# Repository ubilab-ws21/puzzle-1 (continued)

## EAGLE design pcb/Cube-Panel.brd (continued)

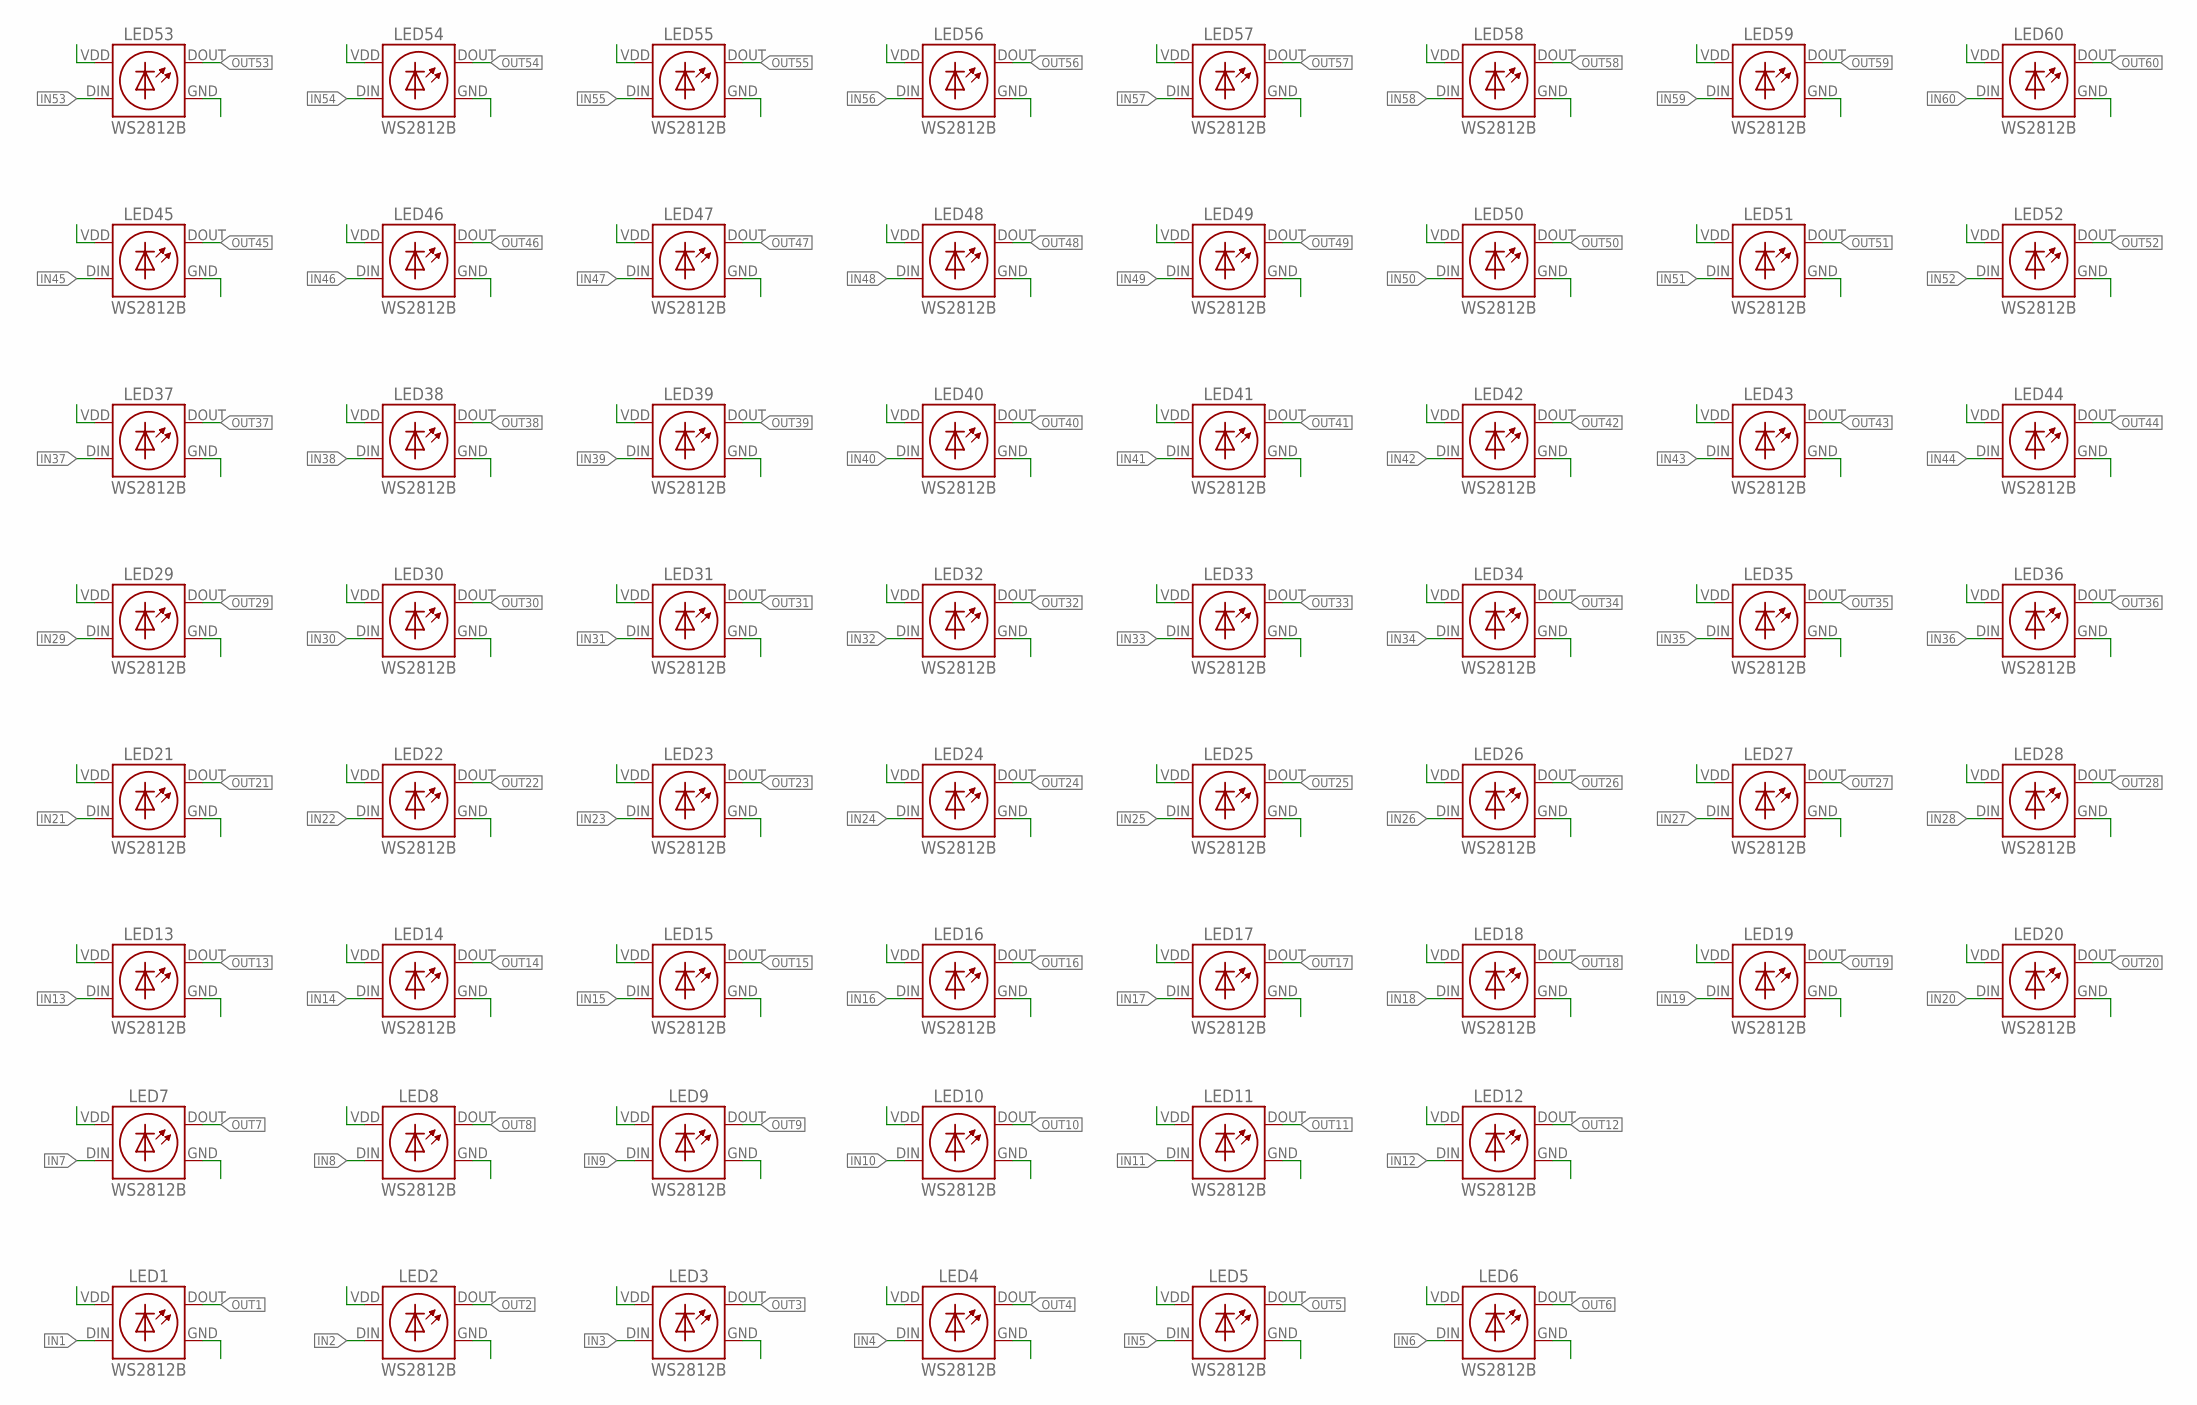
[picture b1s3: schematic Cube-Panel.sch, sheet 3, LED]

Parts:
LED1, LED2, LED3, LED4, LED5, LED6, LED7, LED8, LED9, LED10, LED11, LED12, LED13, LED14, LED15, LED16, LED17, LED18, LED19, LED20, LED21, LED22, LED23, LED24, LED25, LED26, LED27, LED28, LED29, LED30, LED31, LED32, LED33, LED34, LED35, LED36, LED37, LED38, LED39, LED40, LED41, LED42, LED43, LED44, LED45, LED46, LED47, LED48, LED49, LED50, LED51, LED52, LED53, LED54, LED55, LED56, LED57, LED58, LED59, LED60: WS2812B

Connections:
GND: LED1.GND, LED2.GND, LED3.GND, LED4.GND, LED5.GND, LED6.GND, LED7.GND, LED8.GND, LED9.GND, LED10.GND, LED11.GND, LED12.GND, LED13.GND, LED14.GND, LED15.GND, LED16.GND, LED17.GND, LED18.GND, LED19.GND, LED20.GND, LED21.GND, LED22.GND, LED23.GND, LED24.GND, LED25.GND, LED26.GND, LED27.GND, LED28.GND, LED29.GND, LED30.GND, LED31.GND, LED32.GND, LED33.GND, LED34.GND, LED35.GND, LED36.GND, LED37.GND, LED38.GND, LED39.GND, LED40.GND, LED41.GND, LED42.GND, LED43.GND, LED44.GND, LED45.GND, LED46.GND, LED47.GND, LED48.GND, LED49.GND, LED50.GND, LED51.GND, LED52.GND, LED53.GND, LED54.GND, LED55.GND, LED56.GND, LED57.GND, LED58.GND, LED59.GND, LED60.GND; also elsewhere on the board
IN1: LED1.DIN; also elsewhere on the board
IN2: LED2.DIN; also elsewhere on the board
IN3: LED3.DIN; also elsewhere on the board
IN4: LED4.DIN; also elsewhere on the board
IN5: LED5.DIN; also elsewhere on the board
IN6: LED6.DIN; also elsewhere on the board
IN7: LED7.DIN; also elsewhere on the board
IN8: LED8.DIN; also elsewhere on the board
IN9: LED9.DIN; also elsewhere on the board
IN10: LED10.DIN; also elsewhere on the board
IN11: LED11.DIN; also elsewhere on the board
IN12: LED12.DIN; also elsewhere on the board
IN13: LED13.DIN; also elsewhere on the board
IN14: LED14.DIN; also elsewhere on the board
IN15: LED15.DIN; also elsewhere on the board
IN16: LED16.DIN; also elsewhere on the board
IN17: LED17.DIN; also elsewhere on the board
IN18: LED18.DIN; also elsewhere on the board
IN19: LED19.DIN; also elsewhere on the board
IN20: LED20.DIN; also elsewhere on the board
IN21: LED21.DIN; also elsewhere on the board
IN22: LED22.DIN; also elsewhere on the board
IN23: LED23.DIN; also elsewhere on the board
IN24: LED24.DIN; also elsewhere on the board
IN25: LED25.DIN; also elsewhere on the board
IN26: LED26.DIN; also elsewhere on the board
IN27: LED27.DIN; also elsewhere on the board
IN28: LED28.DIN; also elsewhere on the board
IN29: LED29.DIN; also elsewhere on the board
IN30: LED30.DIN; also elsewhere on the board
IN31: LED31.DIN; also elsewhere on the board
IN32: LED32.DIN; also elsewhere on the board
IN33: LED33.DIN; also elsewhere on the board
IN34: LED34.DIN; also elsewhere on the board
IN35: LED35.DIN; also elsewhere on the board
IN36: LED36.DIN; also elsewhere on the board
IN37: LED37.DIN; also elsewhere on the board
IN38: LED38.DIN; also elsewhere on the board
IN39: LED39.DIN; also elsewhere on the board
IN40: LED40.DIN; also elsewhere on the board
IN41: LED41.DIN; also elsewhere on the board
IN42: LED42.DIN; also elsewhere on the board
IN43: LED43.DIN; also elsewhere on the board
IN44: LED44.DIN; also elsewhere on the board
IN45: LED45.DIN; also elsewhere on the board
IN46: LED46.DIN; also elsewhere on the board
IN47: LED47.DIN; also elsewhere on the board
IN48: LED48.DIN; also elsewhere on the board
IN49: LED49.DIN; also elsewhere on the board
IN50: LED50.DIN; also elsewhere on the board
IN51: LED51.DIN; also elsewhere on the board
IN52: LED52.DIN; also elsewhere on the board
IN53: LED53.DIN; also elsewhere on the board
IN54: LED54.DIN; also elsewhere on the board
IN55: LED55.DIN; also elsewhere on the board
IN56: LED56.DIN; also elsewhere on the board
IN57: LED57.DIN; also elsewhere on the board
IN58: LED58.DIN; also elsewhere on the board
IN59: LED59.DIN; also elsewhere on the board
IN60: LED60.DIN; also elsewhere on the board
OUT1: LED1.DOUT; also elsewhere on the board
OUT2: LED2.DOUT; also elsewhere on the board
OUT3: LED3.DOUT; also elsewhere on the board
OUT4: LED4.DOUT; also elsewhere on the board
OUT5: LED5.DOUT; also elsewhere on the board
OUT6: LED6.DOUT; also elsewhere on the board
OUT7: LED7.DOUT; also elsewhere on the board
OUT8: LED8.DOUT; also elsewhere on the board
OUT9: LED9.DOUT; also elsewhere on the board
OUT10: LED10.DOUT; also elsewhere on the board
OUT11: LED11.DOUT; also elsewhere on the board
OUT12: LED12.DOUT; also elsewhere on the board
OUT13: LED13.DOUT; also elsewhere on the board
OUT14: LED14.DOUT; also elsewhere on the board
OUT15: LED15.DOUT; also elsewhere on the board
OUT16: LED16.DOUT; also elsewhere on the board
OUT17: LED17.DOUT; also elsewhere on the board
OUT18: LED18.DOUT; also elsewhere on the board
OUT19: LED19.DOUT; also elsewhere on the board
OUT20: LED20.DOUT; also elsewhere on the board
OUT21: LED21.DOUT; also elsewhere on the board
OUT22: LED22.DOUT; also elsewhere on the board
OUT23: LED23.DOUT; also elsewhere on the board
OUT24: LED24.DOUT; also elsewhere on the board
OUT25: LED25.DOUT; also elsewhere on the board
OUT26: LED26.DOUT; also elsewhere on the board
OUT27: LED27.DOUT; also elsewhere on the board
OUT28: LED28.DOUT; also elsewhere on the board
OUT29: LED29.DOUT; also elsewhere on the board
OUT30: LED30.DOUT; also elsewhere on the board
OUT31: LED31.DOUT; also elsewhere on the board
OUT32: LED32.DOUT; also elsewhere on the board
OUT33: LED33.DOUT; also elsewhere on the board
OUT34: LED34.DOUT; also elsewhere on the board
OUT35: LED35.DOUT; also elsewhere on the board
OUT36: LED36.DOUT; also elsewhere on the board
OUT37: LED37.DOUT; also elsewhere on the board
OUT38: LED38.DOUT; also elsewhere on the board
OUT39: LED39.DOUT; also elsewhere on the board
OUT40: LED40.DOUT; also elsewhere on the board
OUT41: LED41.DOUT; also elsewhere on the board
OUT42: LED42.DOUT; also elsewhere on the board
OUT43: LED43.DOUT; also elsewhere on the board
OUT44: LED44.DOUT; also elsewhere on the board
OUT45: LED45.DOUT; also elsewhere on the board
OUT46: LED46.DOUT; also elsewhere on the board
OUT47: LED47.DOUT; also elsewhere on the board
OUT48: LED48.DOUT; also elsewhere on the board
OUT49: LED49.DOUT; also elsewhere on the board
OUT50: LED50.DOUT; also elsewhere on the board
OUT51: LED51.DOUT; also elsewhere on the board
OUT52: LED52.DOUT; also elsewhere on the board
OUT53: LED53.DOUT; also elsewhere on the board
OUT54: LED54.DOUT; also elsewhere on the board
OUT55: LED55.DOUT; also elsewhere on the board
OUT56: LED56.DOUT; also elsewhere on the board
OUT57: LED57.DOUT; also elsewhere on the board
OUT58: LED58.DOUT; also elsewhere on the board
OUT59: LED59.DOUT; also elsewhere on the board
OUT60: LED60.DOUT; also elsewhere on the board
VCC: LED1.VDD (VCC), LED2.VDD (VCC), LED3.VDD (VCC), LED4.VDD (VCC), LED5.VDD (VCC), LED6.VDD (VCC), LED7.VDD (VCC), LED8.VDD (VCC), LED9.VDD (VCC), LED10.VDD (VCC), LED11.VDD (VCC), LED12.VDD (VCC), LED13.VDD (VCC), LED14.VDD (VCC), LED15.VDD (VCC), LED16.VDD (VCC), LED17.VDD (VCC), LED18.VDD (VCC), LED19.VDD (VCC), LED20.VDD (VCC), LED21.VDD (VCC), LED22.VDD (VCC), LED23.VDD (VCC), LED24.VDD (VCC), LED25.VDD (VCC), LED26.VDD (VCC), LED27.VDD (VCC), LED28.VDD (VCC), LED29.VDD (VCC), LED30.VDD (VCC), LED31.VDD (VCC), LED32.VDD (VCC), LED33.VDD (VCC), LED34.VDD (VCC), LED35.VDD (VCC), LED36.VDD (VCC), LED37.VDD (VCC), LED38.VDD (VCC), LED39.VDD (VCC), LED40.VDD (VCC), LED41.VDD (VCC), LED42.VDD (VCC), LED43.VDD (VCC), LED44.VDD (VCC), LED45.VDD (VCC), LED46.VDD (VCC), LED47.VDD (VCC), LED48.VDD (VCC), LED49.VDD (VCC), LED50.VDD (VCC), LED51.VDD (VCC), LED52.VDD (VCC), LED53.VDD (VCC), LED54.VDD (VCC), LED55.VDD (VCC), LED56.VDD (VCC), LED57.VDD (VCC), LED58.VDD (VCC), LED59.VDD (VCC), LED60.VDD (VCC); also elsewhere on the board

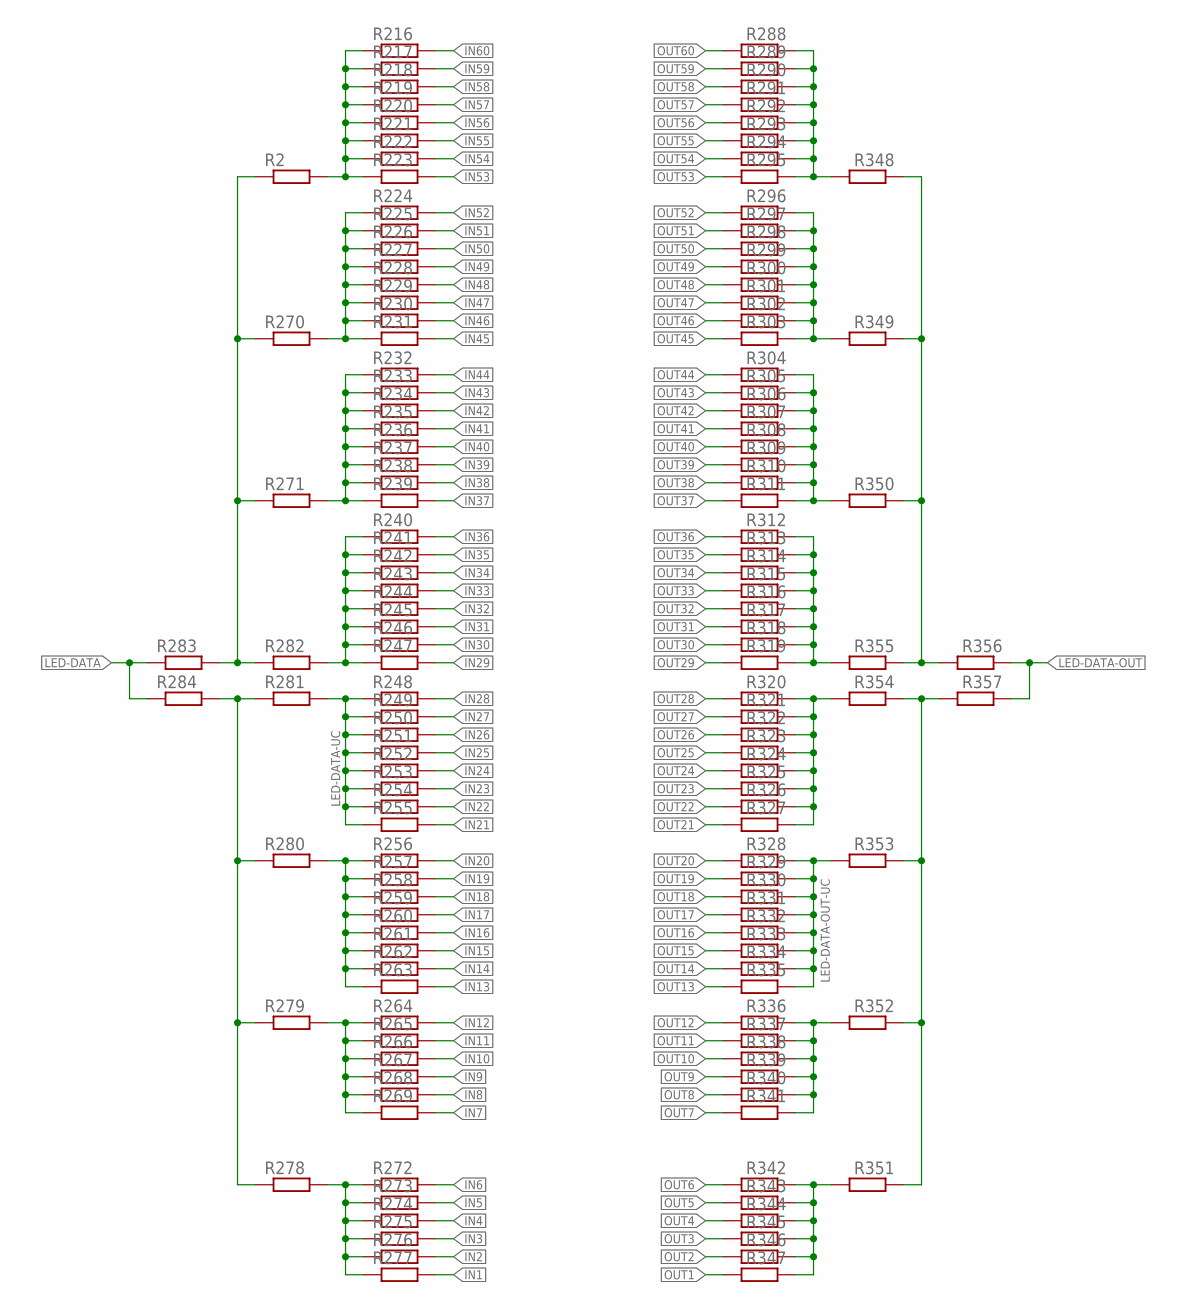
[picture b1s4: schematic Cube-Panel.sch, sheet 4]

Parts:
R2, R216, R217, R218, R219, R220, R221, R222, R223, R224, R225, R226, R227, R228, R229, R230, R231, R232, R233, R234, R235, R236, R237, R238, R239, R240, R241, R242, R243, R244, R245, R246, R247, R248, R249, R250, R251, R252, R253, R254, R255, R256, R257, R258, R259, R260, R261, R262, R263, R264, R265, R266, R267, R268, R269, R270, R271, R272, R273, R274, R275, R276, R277, R278, R279, R280, R281, R282, R283, R284, R288, R289, R290, R291, R292, R293, R294, R295, R296, R297, R298, R299, R300, R301, R302, R303, R304, R305, R306, R307, R308, R309, R310, R311, R312, R313, R314, R315, R316, R317, R318, R319, R320, R321, R322, R323, R324, R325, R326, R327, R328, R329, R330, R331, R332, R333, R334, R335, R336, R337, R338, R339, R340, R341, R342, R343, R344, R345, R346, R347, R348, R349, R350, R351, R352, R353, R354, R355, R356, R357: WIDERSTAND-0603; 0603

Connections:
IN1: R277.P$2 (2); also elsewhere on the board
IN2: R276.P$2 (2); also elsewhere on the board
IN3: R275.P$2 (2); also elsewhere on the board
IN4: R274.P$2 (2); also elsewhere on the board
IN5: R273.P$2 (2); also elsewhere on the board
IN6: R272.P$2 (2); also elsewhere on the board
IN7: R269.P$2 (2); also elsewhere on the board
IN8: R268.P$2 (2); also elsewhere on the board
IN9: R267.P$2 (2); also elsewhere on the board
IN10: R266.P$2 (2); also elsewhere on the board
IN11: R265.P$2 (2); also elsewhere on the board
IN12: R264.P$2 (2); also elsewhere on the board
IN13: R263.P$2 (2); also elsewhere on the board
IN14: R262.P$2 (2); also elsewhere on the board
IN15: R261.P$2 (2); also elsewhere on the board
IN16: R260.P$2 (2); also elsewhere on the board
IN17: R259.P$2 (2); also elsewhere on the board
IN18: R258.P$2 (2); also elsewhere on the board
IN19: R257.P$2 (2); also elsewhere on the board
IN20: R256.P$2 (2); also elsewhere on the board
IN21: R255.P$2 (2); also elsewhere on the board
IN22: R254.P$2 (2); also elsewhere on the board
IN23: R253.P$2 (2); also elsewhere on the board
IN24: R252.P$2 (2); also elsewhere on the board
IN25: R251.P$2 (2); also elsewhere on the board
IN26: R250.P$2 (2); also elsewhere on the board
IN27: R249.P$2 (2); also elsewhere on the board
IN28: R248.P$2 (2); also elsewhere on the board
IN29: R247.P$2 (2); also elsewhere on the board
IN30: R246.P$2 (2); also elsewhere on the board
IN31: R245.P$2 (2); also elsewhere on the board
IN32: R244.P$2 (2); also elsewhere on the board
IN33: R243.P$2 (2); also elsewhere on the board
IN34: R242.P$2 (2); also elsewhere on the board
IN35: R241.P$2 (2); also elsewhere on the board
IN36: R240.P$2 (2); also elsewhere on the board
IN37: R239.P$2 (2); also elsewhere on the board
IN38: R238.P$2 (2); also elsewhere on the board
IN39: R237.P$2 (2); also elsewhere on the board
IN40: R236.P$2 (2); also elsewhere on the board
IN41: R235.P$2 (2); also elsewhere on the board
IN42: R234.P$2 (2); also elsewhere on the board
IN43: R233.P$2 (2); also elsewhere on the board
IN44: R232.P$2 (2); also elsewhere on the board
IN45: R231.P$2 (2); also elsewhere on the board
IN46: R230.P$2 (2); also elsewhere on the board
IN47: R229.P$2 (2); also elsewhere on the board
IN48: R228.P$2 (2); also elsewhere on the board
IN49: R227.P$2 (2); also elsewhere on the board
IN50: R226.P$2 (2); also elsewhere on the board
IN51: R225.P$2 (2); also elsewhere on the board
IN52: R224.P$2 (2); also elsewhere on the board
IN53: R223.P$2 (2); also elsewhere on the board
IN54: R222.P$2 (2); also elsewhere on the board
IN55: R221.P$2 (2); also elsewhere on the board
IN56: R220.P$2 (2); also elsewhere on the board
IN57: R219.P$2 (2); also elsewhere on the board
IN58: R218.P$2 (2); also elsewhere on the board
IN59: R217.P$2 (2); also elsewhere on the board
IN60: R216.P$2 (2); also elsewhere on the board
LED-DATA: R283.P$1 (1), R284.P$1 (1); also elsewhere on the board
LED-DATA-OUT: R356.P$1 (1), R357.P$1 (1); also elsewhere on the board
LED-DATA-OUT-UC: R328.P$1 (1), R329.P$1 (1), R330.P$1 (1), R331.P$1 (1), R332.P$1 (1), R333.P$1 (1), R334.P$1 (1), R335.P$1 (1), R353.P$2 (2); also elsewhere on the board
LED-DATA-UC: R248.P$1 (1), R249.P$1 (1), R250.P$1 (1), R251.P$1 (1), R252.P$1 (1), R253.P$1 (1), R254.P$1 (1), R255.P$1 (1), R281.P$2 (2); also elsewhere on the board
unnamed: R278.P$1 (1), R279.P$1 (1), R280.P$1 (1), R281.P$1 (1), R284.P$2 (2)
unnamed: R2.P$1 (1), R270.P$1 (1), R271.P$1 (1), R282.P$1 (1), R283.P$2 (2)
unnamed: R288.P$1 (1), R289.P$1 (1), R290.P$1 (1), R291.P$1 (1), R292.P$1 (1), R293.P$1 (1), R294.P$1 (1), R295.P$1 (1), R348.P$2 (2)
unnamed: R296.P$1 (1), R297.P$1 (1), R298.P$1 (1), R299.P$1 (1), R300.P$1 (1), R301.P$1 (1), R302.P$1 (1), R303.P$1 (1), R349.P$2 (2)
unnamed: R304.P$1 (1), R305.P$1 (1), R306.P$1 (1), R307.P$1 (1), R308.P$1 (1), R309.P$1 (1), R310.P$1 (1), R311.P$1 (1), R350.P$2 (2)
unnamed: R312.P$1 (1), R313.P$1 (1), R314.P$1 (1), R315.P$1 (1), R316.P$1 (1), R317.P$1 (1), R318.P$1 (1), R319.P$1 (1), R355.P$2 (2)
unnamed: R320.P$1 (1), R321.P$1 (1), R322.P$1 (1), R323.P$1 (1), R324.P$1 (1), R325.P$1 (1), R326.P$1 (1), R327.P$1 (1), R354.P$2 (2)
unnamed: R2.P$2 (2), R216.P$1 (1), R217.P$1 (1), R218.P$1 (1), R219.P$1 (1), R220.P$1 (1), R221.P$1 (1), R222.P$1 (1), R223.P$1 (1)
unnamed: R336.P$1 (1), R337.P$1 (1), R338.P$1 (1), R339.P$1 (1), R340.P$1 (1), R341.P$1 (1), R352.P$2 (2)
unnamed: R342.P$1 (1), R343.P$1 (1), R344.P$1 (1), R345.P$1 (1), R346.P$1 (1), R347.P$1 (1), R351.P$2 (2)
unnamed: R351.P$1 (1), R352.P$1 (1), R353.P$1 (1), R354.P$1 (1), R357.P$2 (2)
unnamed: R348.P$1 (1), R349.P$1 (1), R350.P$1 (1), R355.P$1 (1), R356.P$2 (2)
unnamed: R224.P$1 (1), R225.P$1 (1), R226.P$1 (1), R227.P$1 (1), R228.P$1 (1), R229.P$1 (1), R230.P$1 (1), R231.P$1 (1), R270.P$2 (2)
unnamed: R232.P$1 (1), R233.P$1 (1), R234.P$1 (1), R235.P$1 (1), R236.P$1 (1), R237.P$1 (1), R238.P$1 (1), R239.P$1 (1), R271.P$2 (2)
unnamed: R240.P$1 (1), R241.P$1 (1), R242.P$1 (1), R243.P$1 (1), R244.P$1 (1), R245.P$1 (1), R246.P$1 (1), R247.P$1 (1), R282.P$2 (2)
unnamed: R256.P$1 (1), R257.P$1 (1), R258.P$1 (1), R259.P$1 (1), R260.P$1 (1), R261.P$1 (1), R262.P$1 (1), R263.P$1 (1), R280.P$2 (2)
unnamed: R264.P$1 (1), R265.P$1 (1), R266.P$1 (1), R267.P$1 (1), R268.P$1 (1), R269.P$1 (1), R279.P$2 (2)
unnamed: R272.P$1 (1), R273.P$1 (1), R274.P$1 (1), R275.P$1 (1), R276.P$1 (1), R277.P$1 (1), R278.P$2 (2)
OUT1: R347.P$2 (2); also elsewhere on the board
OUT2: R346.P$2 (2); also elsewhere on the board
OUT3: R345.P$2 (2); also elsewhere on the board
OUT4: R344.P$2 (2); also elsewhere on the board
OUT5: R343.P$2 (2); also elsewhere on the board
OUT6: R342.P$2 (2); also elsewhere on the board
OUT7: R341.P$2 (2); also elsewhere on the board
OUT8: R340.P$2 (2); also elsewhere on the board
OUT9: R339.P$2 (2); also elsewhere on the board
OUT10: R338.P$2 (2); also elsewhere on the board
OUT11: R337.P$2 (2); also elsewhere on the board
OUT12: R336.P$2 (2); also elsewhere on the board
OUT13: R335.P$2 (2); also elsewhere on the board
OUT14: R334.P$2 (2); also elsewhere on the board
OUT15: R333.P$2 (2); also elsewhere on the board
OUT16: R332.P$2 (2); also elsewhere on the board
OUT17: R331.P$2 (2); also elsewhere on the board
OUT18: R330.P$2 (2); also elsewhere on the board
OUT19: R329.P$2 (2); also elsewhere on the board
OUT20: R328.P$2 (2); also elsewhere on the board
OUT21: R327.P$2 (2); also elsewhere on the board
OUT22: R326.P$2 (2); also elsewhere on the board
OUT23: R325.P$2 (2); also elsewhere on the board
OUT24: R324.P$2 (2); also elsewhere on the board
OUT25: R323.P$2 (2); also elsewhere on the board
OUT26: R322.P$2 (2); also elsewhere on the board
OUT27: R321.P$2 (2); also elsewhere on the board
OUT28: R320.P$2 (2); also elsewhere on the board
OUT29: R319.P$2 (2); also elsewhere on the board
OUT30: R318.P$2 (2); also elsewhere on the board
OUT31: R317.P$2 (2); also elsewhere on the board
OUT32: R316.P$2 (2); also elsewhere on the board
OUT33: R315.P$2 (2); also elsewhere on the board
OUT34: R314.P$2 (2); also elsewhere on the board
OUT35: R313.P$2 (2); also elsewhere on the board
OUT36: R312.P$2 (2); also elsewhere on the board
OUT37: R311.P$2 (2); also elsewhere on the board
OUT38: R310.P$2 (2); also elsewhere on the board
OUT39: R309.P$2 (2); also elsewhere on the board
OUT40: R308.P$2 (2); also elsewhere on the board
OUT41: R307.P$2 (2); also elsewhere on the board
OUT42: R306.P$2 (2); also elsewhere on the board
OUT43: R305.P$2 (2); also elsewhere on the board
OUT44: R304.P$2 (2); also elsewhere on the board
OUT45: R303.P$2 (2); also elsewhere on the board
OUT46: R302.P$2 (2); also elsewhere on the board
OUT47: R301.P$2 (2); also elsewhere on the board
OUT48: R300.P$2 (2); also elsewhere on the board
OUT49: R299.P$2 (2); also elsewhere on the board
OUT50: R298.P$2 (2); also elsewhere on the board
OUT51: R297.P$2 (2); also elsewhere on the board
OUT52: R296.P$2 (2); also elsewhere on the board
OUT53: R295.P$2 (2); also elsewhere on the board
OUT54: R294.P$2 (2); also elsewhere on the board
OUT55: R293.P$2 (2); also elsewhere on the board
OUT56: R292.P$2 (2); also elsewhere on the board
OUT57: R291.P$2 (2); also elsewhere on the board
OUT58: R290.P$2 (2); also elsewhere on the board
OUT59: R289.P$2 (2); also elsewhere on the board
OUT60: R288.P$2 (2); also elsewhere on the board

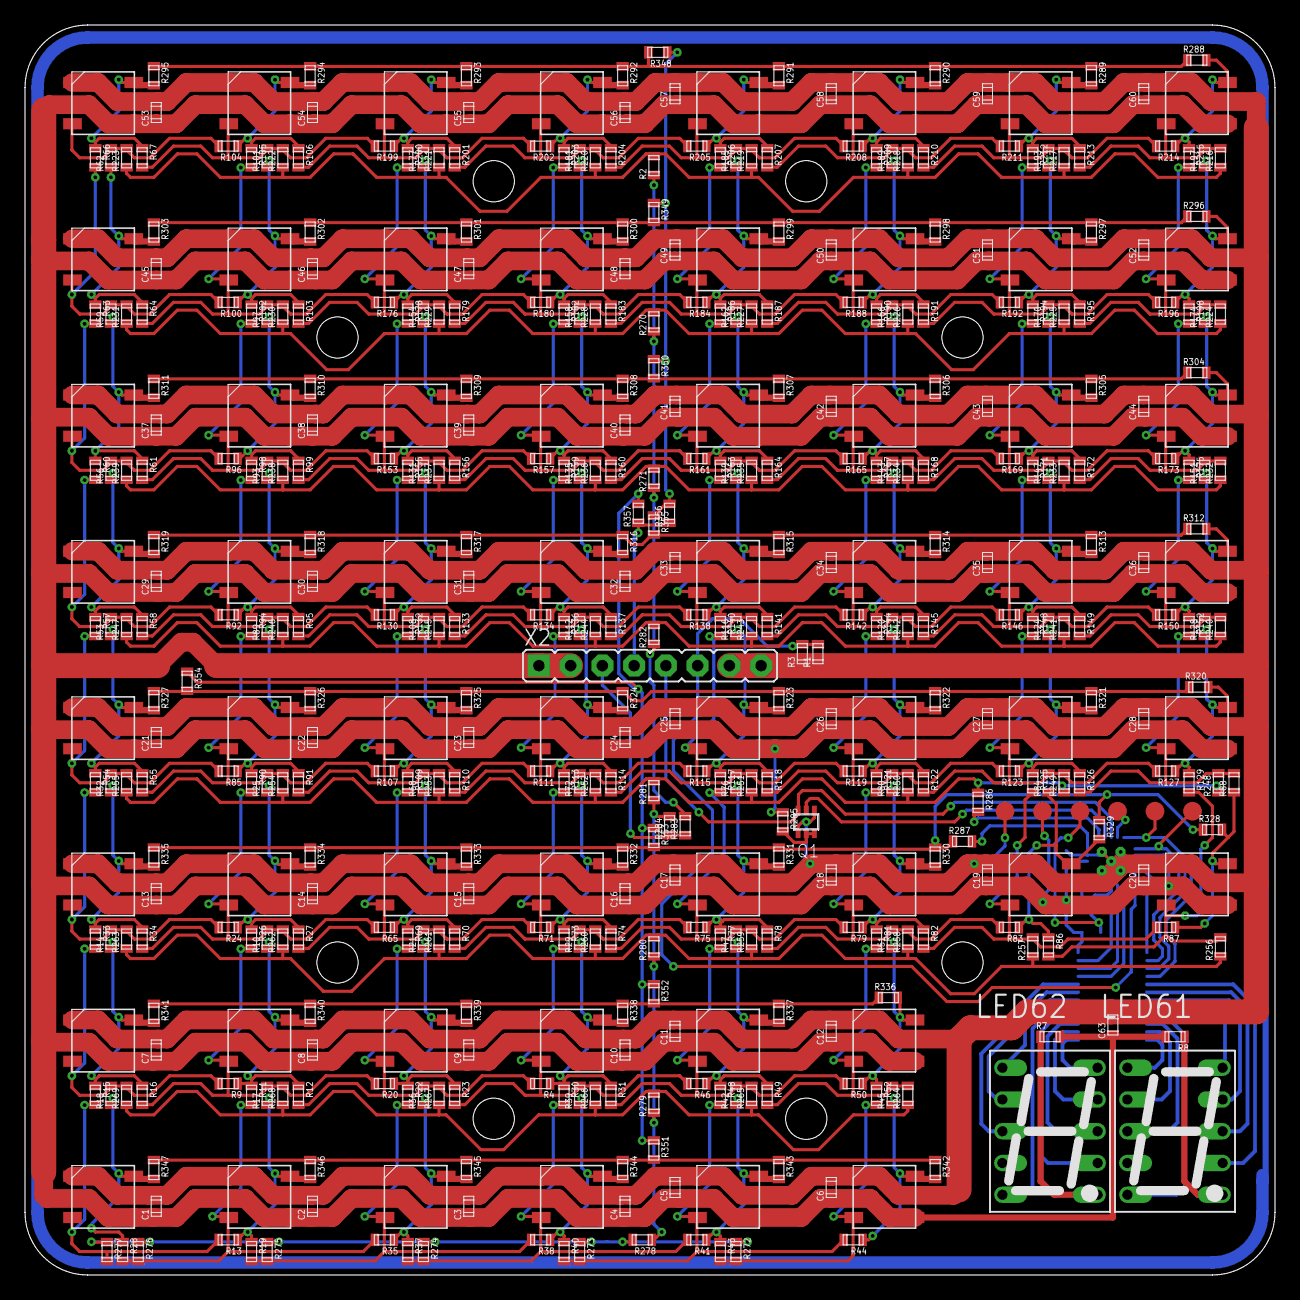
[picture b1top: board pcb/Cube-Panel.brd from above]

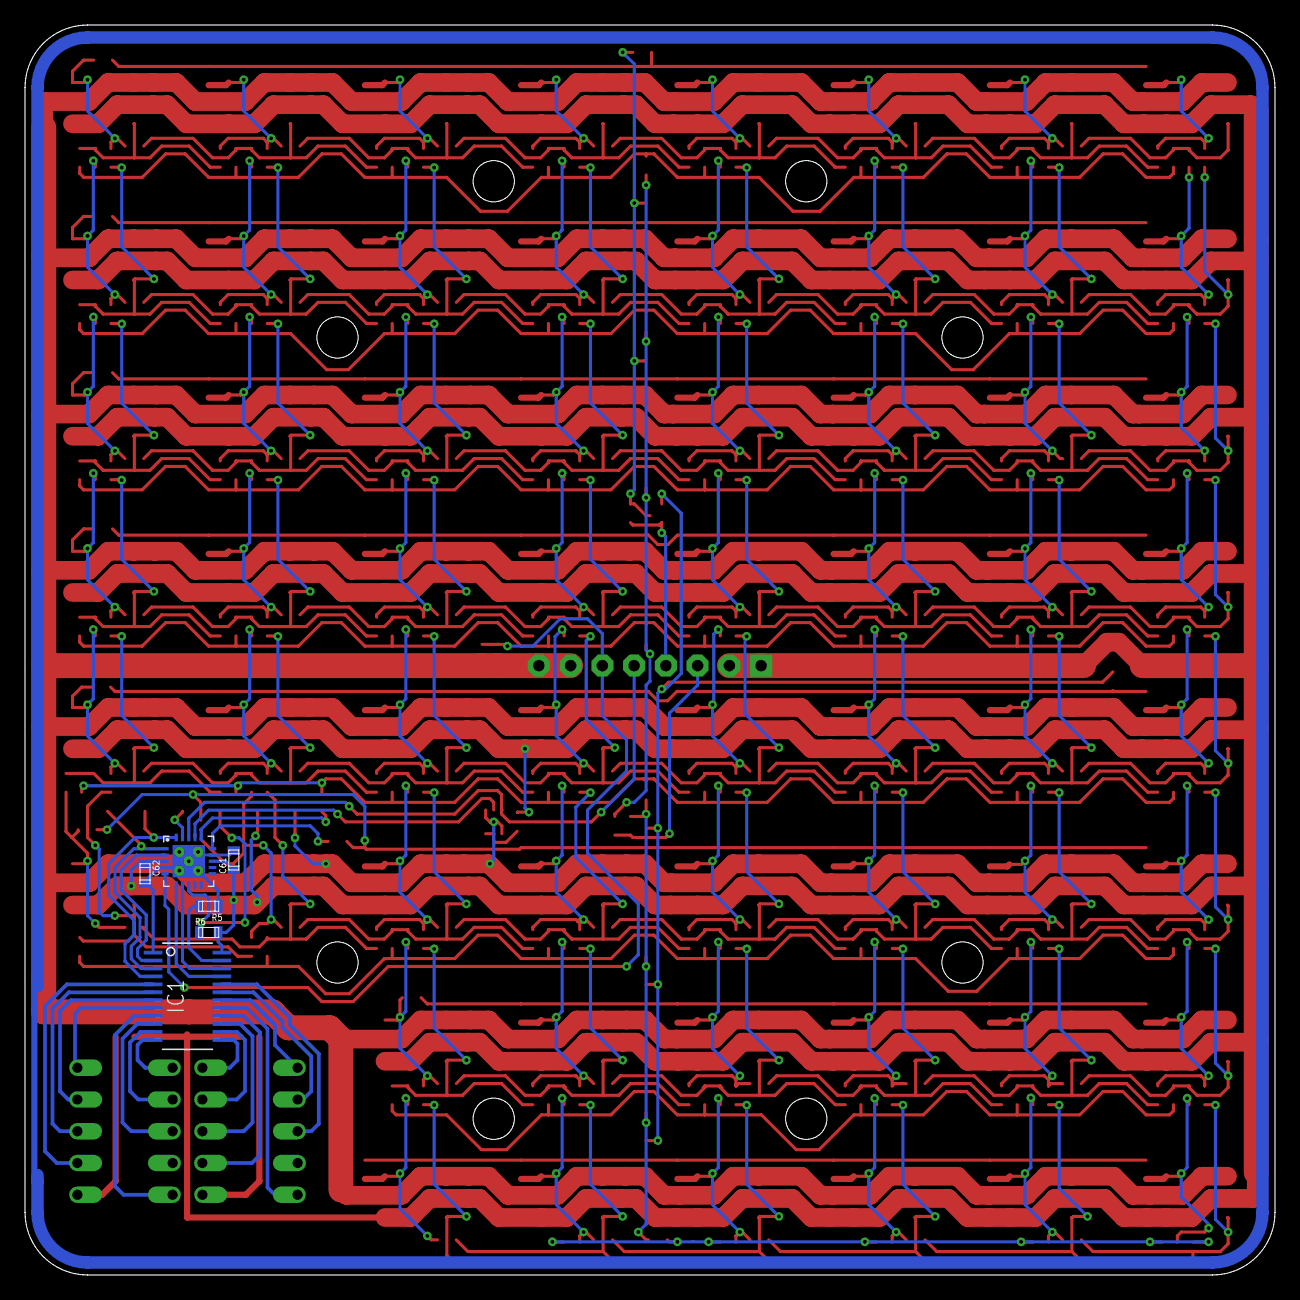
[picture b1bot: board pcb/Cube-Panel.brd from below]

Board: 2 copper layers, 100.0 x 100.0 mm, 492 parts (6 on the bottom side), 176 nets.
